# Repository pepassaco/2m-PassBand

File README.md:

# Filtro paso banda para 137MHz
Filtro diseñado para trabajar adecuadamente la banda de 2m (VHF). Capaz de cubrir tanto la zona destinada a comunicaciones entre radioaficionados (144MHz-148MHz) como la asociada a los satélites NOAA 15, 18, 19 y Meteor M N2-1 (137MHz-138MHz). 

# Características:

- Tipo de filtro: paso banda, Butterworth modificado para mejor S11 en banda de paso

- Orden: 6

- Frecuencia de corte inferior: 125MHz

- Frecuencia de corte sueprior: 155MHz

- Atenuación banda radiodifusión FM: >50dB

- Inpedancia de entrada: 50Ω

- Inpedancia de salida: 50Ω

**Note**: on the PCB, the 6th stage of the filter includes space for a second inductor. This es due to the unavailability of an inductor of the esact value I needes, so I ended up dividing it into two that added up the original value.

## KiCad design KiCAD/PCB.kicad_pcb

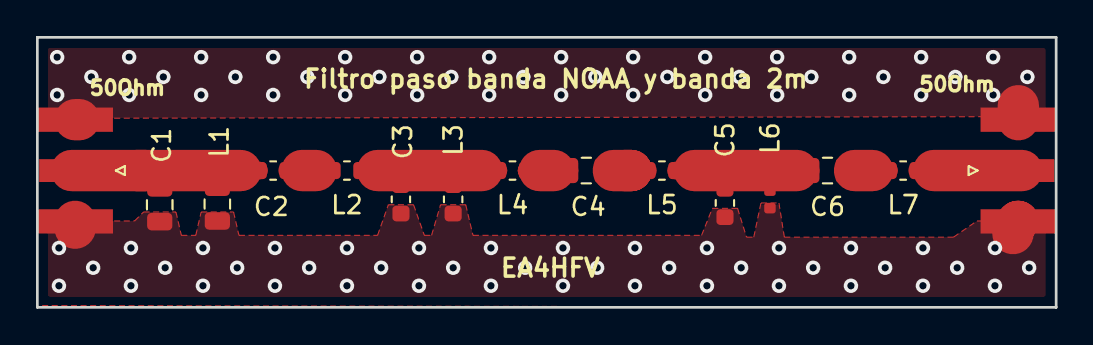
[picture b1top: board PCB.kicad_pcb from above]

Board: 2 copper layers, 56.6 x 15.0 mm, 13 parts (0 on the bottom side), 8 nets.

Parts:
C1: 56pF; C_0805_2012Metric
C2: 3,3pF; C_0603_1608Metric
C3: 220pF; C_0603_1608Metric
C4: 2,7pF; C_0805_2012Metric
C5: 150pF; C_0603_1608Metric
C6: 10pF; C_0805_2012Metric
L1: 22nH; L_0805_2012Metric
L2, L4: 390nH; L_0603_1608Metric
L3: 6,2nH; L_0603_1608Metric
L5: 120nH; L_0603_1608Metric
L6: 9,1nH; L_0402_1005Metric
L7: 130nH; L_0603_1608Metric

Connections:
Earth: C1.2, C3.2, C5.2, L1.2, L3.2, L6.2
unnamed: C1.1, C2.2, L1.1
unnamed: C2.1, L2.2
unnamed: C3.1, L2.1, L3.1, L4.2
unnamed: C4.1, L5.2
unnamed: C4.2, L4.1
unnamed: C5.1, C6.2, L5.1, L6.1
unnamed: C6.1, L7.2

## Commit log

2019-07-11 Rename Elip5.asc to 137MHz-Elliptic-BPF.asc
2019-07-11 Rename LTSpice Simulation/137MHz-Elliptic-BPF.asc to LTSpice files/137MHz-Elliptic-BPF.asc
2019-07-11 Rename LTSpice files/137MHz-Elliptic-BPF.asc to LTSpice/137MHz-Elliptic-BPF.asc
2019-07-11 Create v
2020-07-17 Solventando errores
2020-07-17 Actualizado Readme
2020-07-18 Nueva version del filtro en KiCAD
2020-07-18 Nuevo Readme
